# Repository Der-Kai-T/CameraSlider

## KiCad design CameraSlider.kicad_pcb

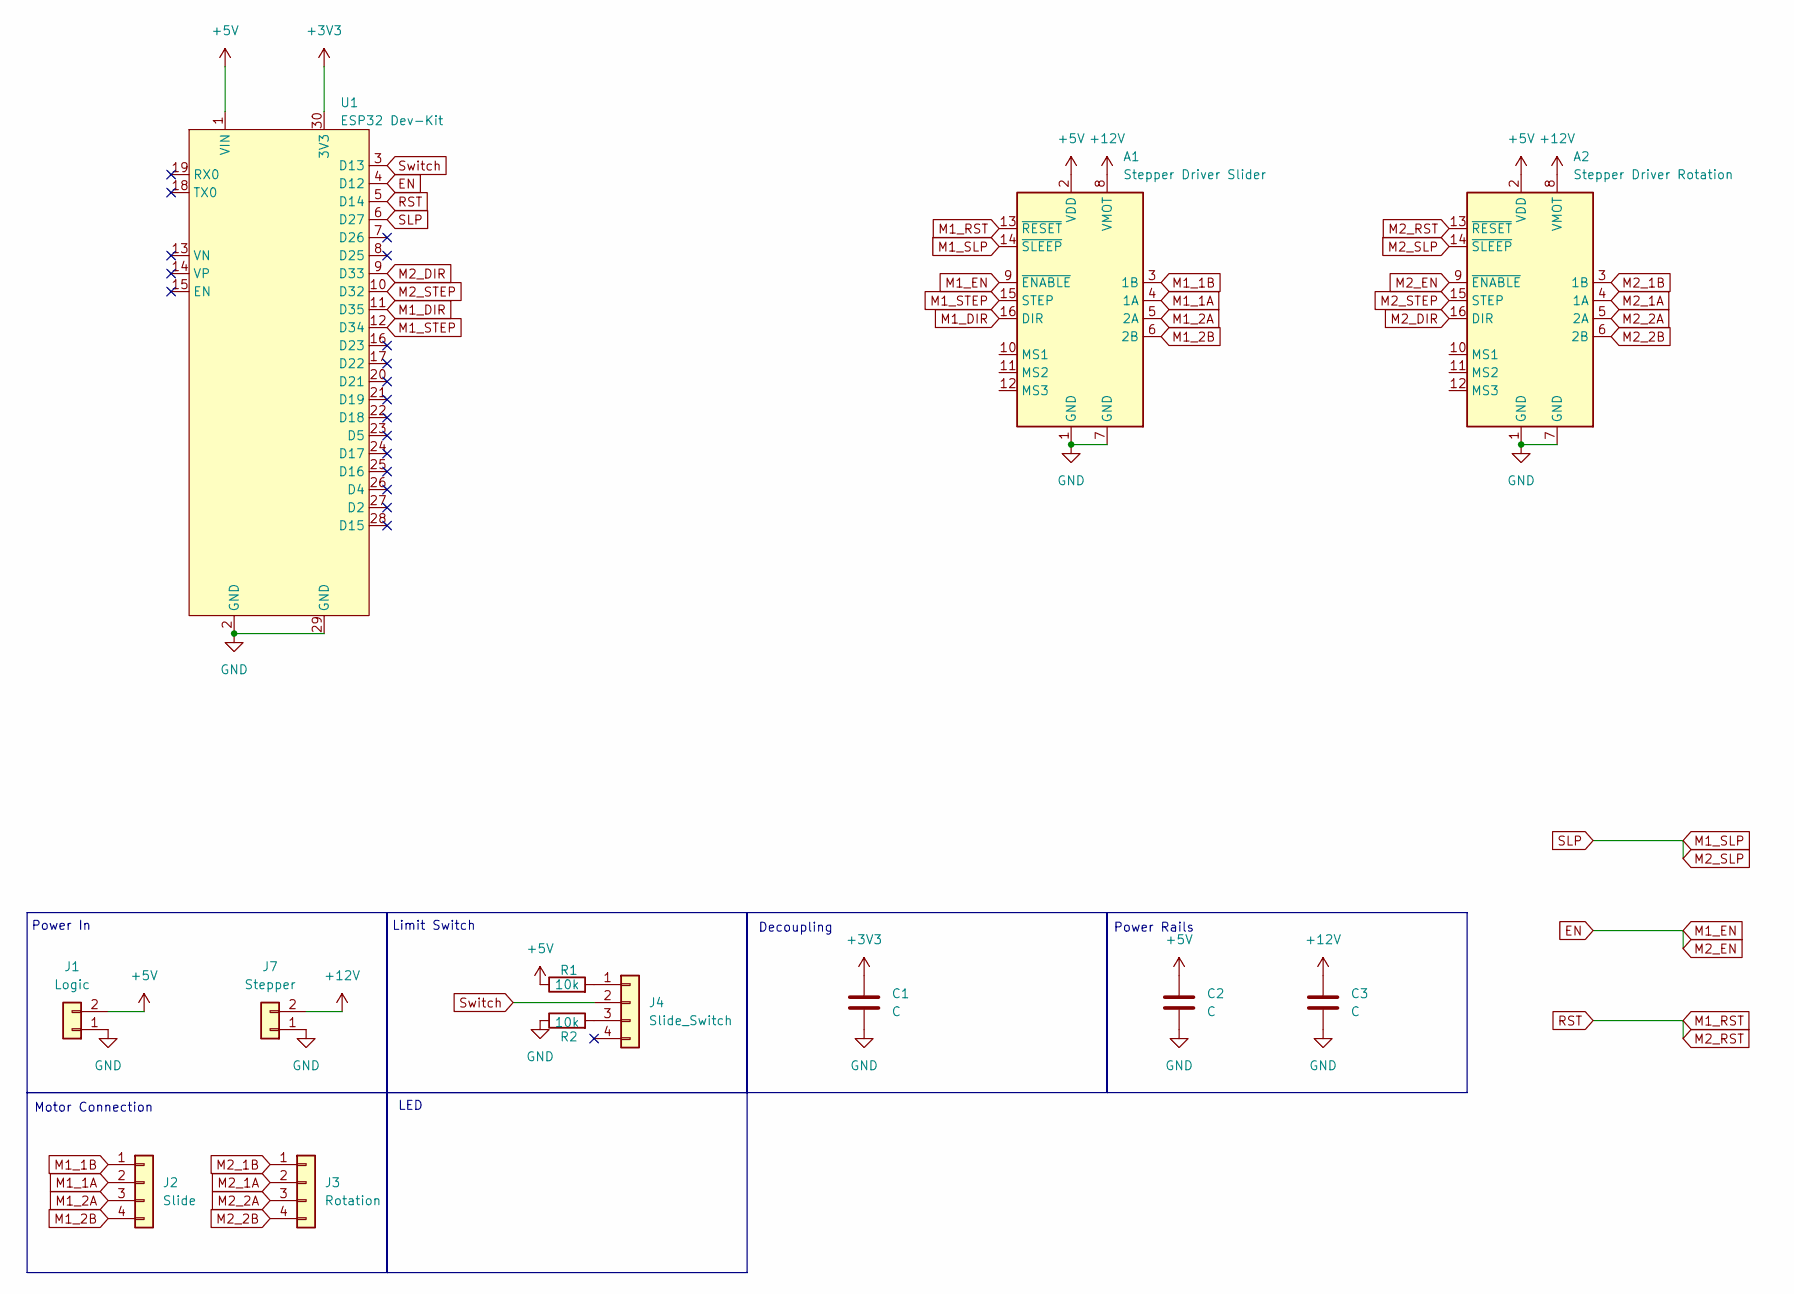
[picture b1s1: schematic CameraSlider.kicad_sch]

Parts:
A1: Stepper Driver Slider; Pololu_Breakout-16_15.2x20.3mm
A2: Stepper Driver Rotation; Pololu_Breakout-16_15.2x20.3mm
C1: C; C_Disc_D3.0mm_W1.6mm_P2.50mm
C2, C3: C; CP_Radial_D6.3mm_P2.50mm
J1: Logic; PinHeader_1x02_P2.54mm_Vertical
J2: Slide; PinHeader_1x04_P2.54mm_Vertical
J3: Rotation; PinHeader_1x04_P2.54mm_Vertical
J4: Slide_Switch; PinHeader_1x04_P2.54mm_Vertical
J7: Stepper; PinHeader_1x02_P2.54mm_Vertical
R1, R2: 10k; R_Axial_DIN0204_L3.6mm_D1.6mm_P7.62mm_Horizontal
U1: ESP32 Dev-Kit; ESP32-USBC-DevBoard

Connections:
+3V3: C1.1, U1.30 (3V3)
+5V: A1.2 (VDD), A2.2 (VDD), C2.1, J1.2, R1.1, U1.1 (VIN)
+12V: A1.8 (VMOT), A2.8 (VMOT), C3.1, J7.2
EN: A1.9 (~ENABLE), A2.9 (~ENABLE), U1.4 (D12)
GND: A1.1 (GND), A1.7 (GND), A2.1 (GND), A2.7 (GND), C1.2, C2.2, C3.2, J1.1, J7.1, R2.1, U1.2 (GND), U1.29 (GND)
M1_1A: A1.4 (1A), J2.2
M1_1B: A1.3 (1B), J2.1
M1_2A: A1.5 (2A), J2.3
M1_2B: A1.6 (2B), J2.4
M1_DIR: A1.16 (DIR), U1.11 (D35)
M1_RST: A1.13 (~RESET), A2.13 (~RESET), U1.5 (D14)
M1_SLP: A1.14 (~SLEEP), A2.14 (~SLEEP), U1.6 (D27)
M1_STEP: A1.15 (STEP), U1.12 (D34)
M2_1A: A2.4 (1A), J3.2
M2_1B: A2.3 (1B), J3.1
M2_2A: A2.5 (2A), J3.3
M2_2B: A2.6 (2B), J3.4
M2_DIR: A2.16 (DIR), U1.9 (D33)
M2_STEP: A2.15 (STEP), U1.10 (D32)
unnamed: J4.1, R1.2
unnamed: J4.3, R2.2
Switch: J4.2, U1.3 (D13)

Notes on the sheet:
Limit Switch
Power Rails
Motor Connection
LED
Power In
Decoupling

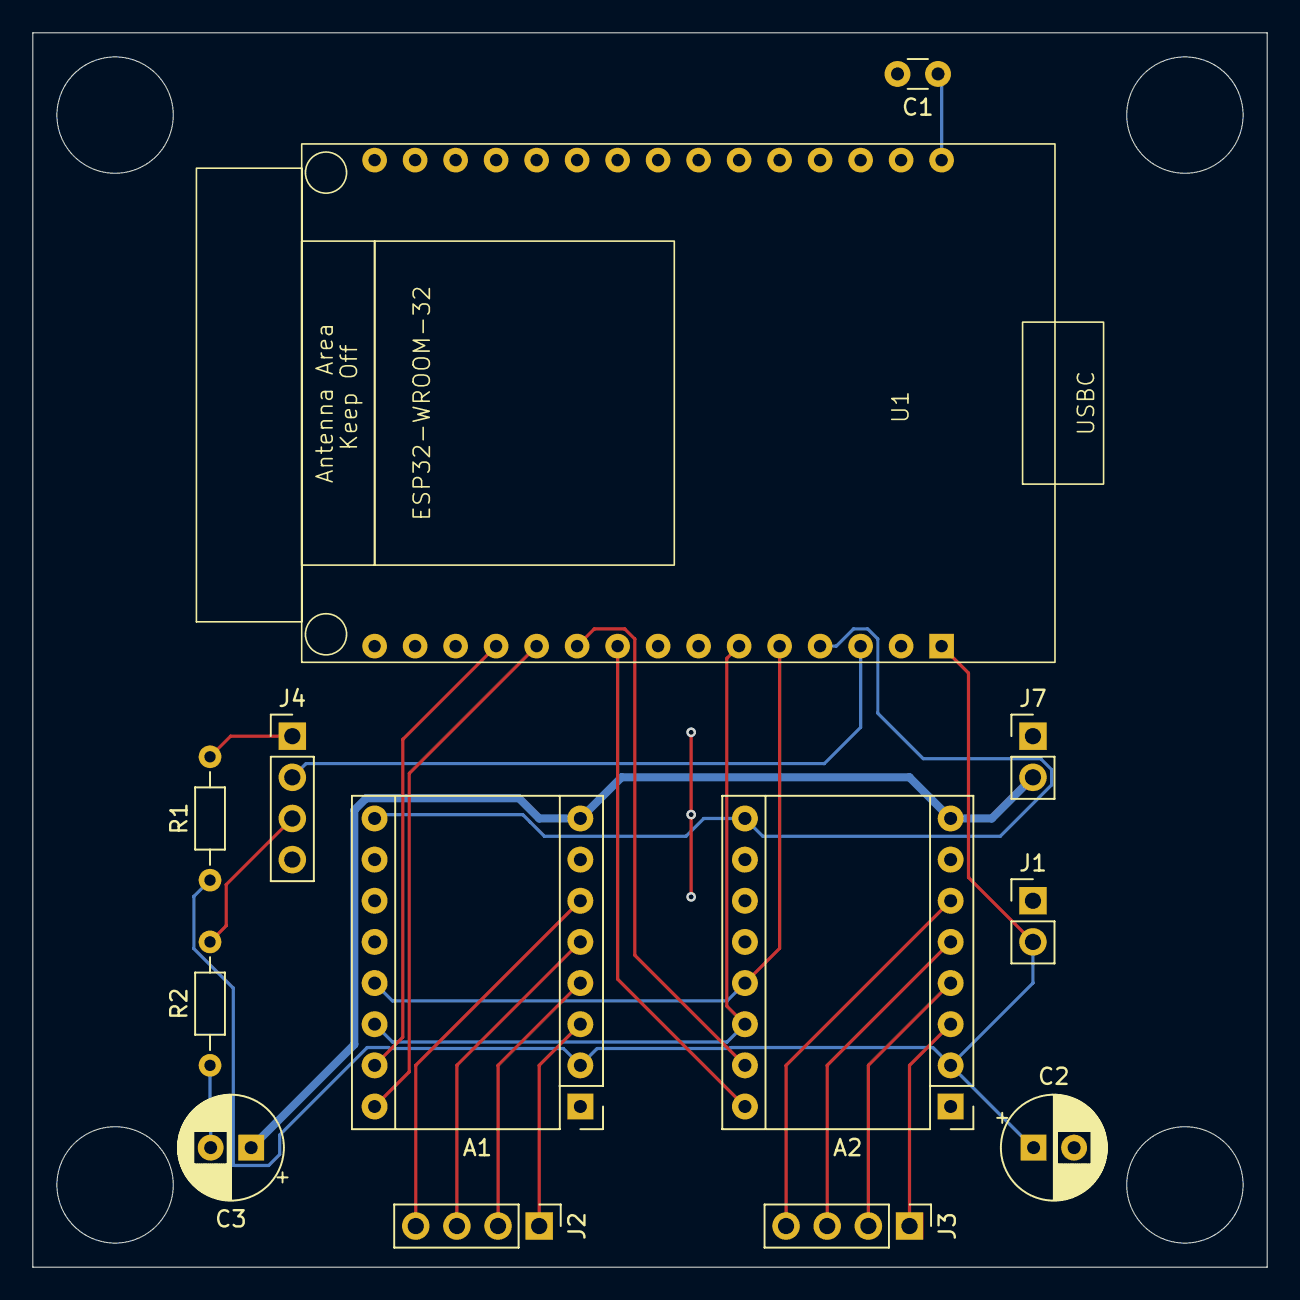
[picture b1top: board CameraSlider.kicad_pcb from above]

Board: 2 copper layers, 76.2 x 76.2 mm, 13 parts (0 on the bottom side), 22 nets.

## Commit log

2024-11-14 RevA
